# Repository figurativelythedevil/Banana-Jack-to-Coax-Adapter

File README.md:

# Banana-Jack-to-Coax-Adapter
 Two stacked boards that convert standard banana jack inputs to coaxial inputs with a common shield. Designed for 4-wire resistance measurements.

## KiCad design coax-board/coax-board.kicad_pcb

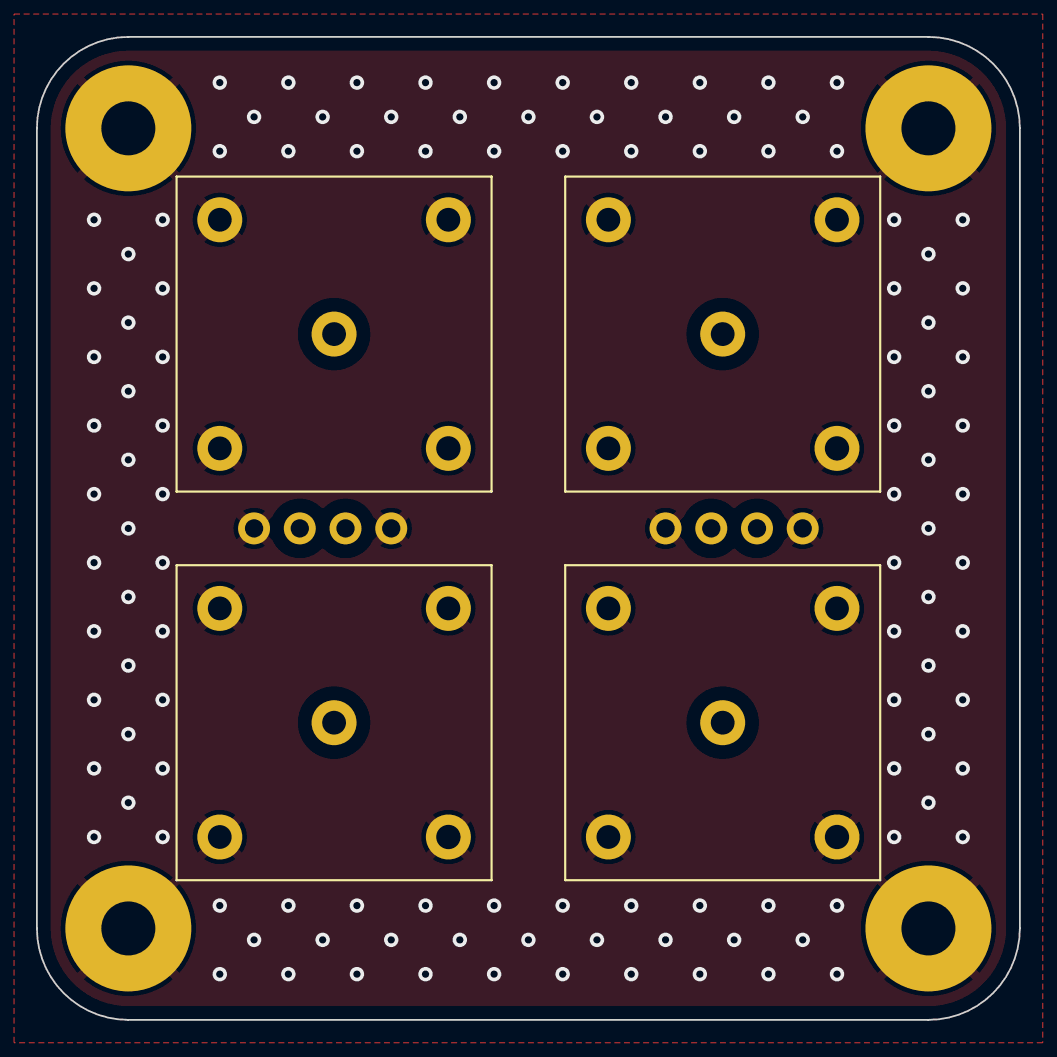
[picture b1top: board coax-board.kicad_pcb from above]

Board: 4 copper layers, 54.6 x 54.6 mm, 10 parts (0 on the bottom side), 5 nets.

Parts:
H1, H2, H3, H4: Mount; m3 mounting pad
J1: Sense Hi; Pomona4578
J2: Force Hi; Pomona4578
J3: Sense Lo; Pomona4578
J3#2, J3#3: Conn_01x02_Male; Pin-Header-01x04-0.1inch-LargeHole
J4: Force Lo; Pomona4578

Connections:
unnamed: J1.1 (In), J3#3.3
unnamed: J2.1 (In), J3#2.2
unnamed: J3.1 (In), J3#3.2
unnamed: J3#2.3, J4.1 (In)
unnamed: H1.1, H2.1, H3.1, H4.1, J1.2 (Ext), J2.2 (Ext), J3.2 (Ext), J3#2.1, J3#3.1, J4.2 (Ext)

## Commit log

2021-09-23 Added all KiCad project files
